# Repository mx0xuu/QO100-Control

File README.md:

# QO100-Control
Transverter control for QO100

## What is it ?
PIC based controller which will generate the required frequencies for both up-converter (DX Patrol) and down-converter. This controller will also use the PTT (SEND) from the IF Transceiver, squence the keying of RX/TX and powering of power amp.

The software is developed for PIC16F18444

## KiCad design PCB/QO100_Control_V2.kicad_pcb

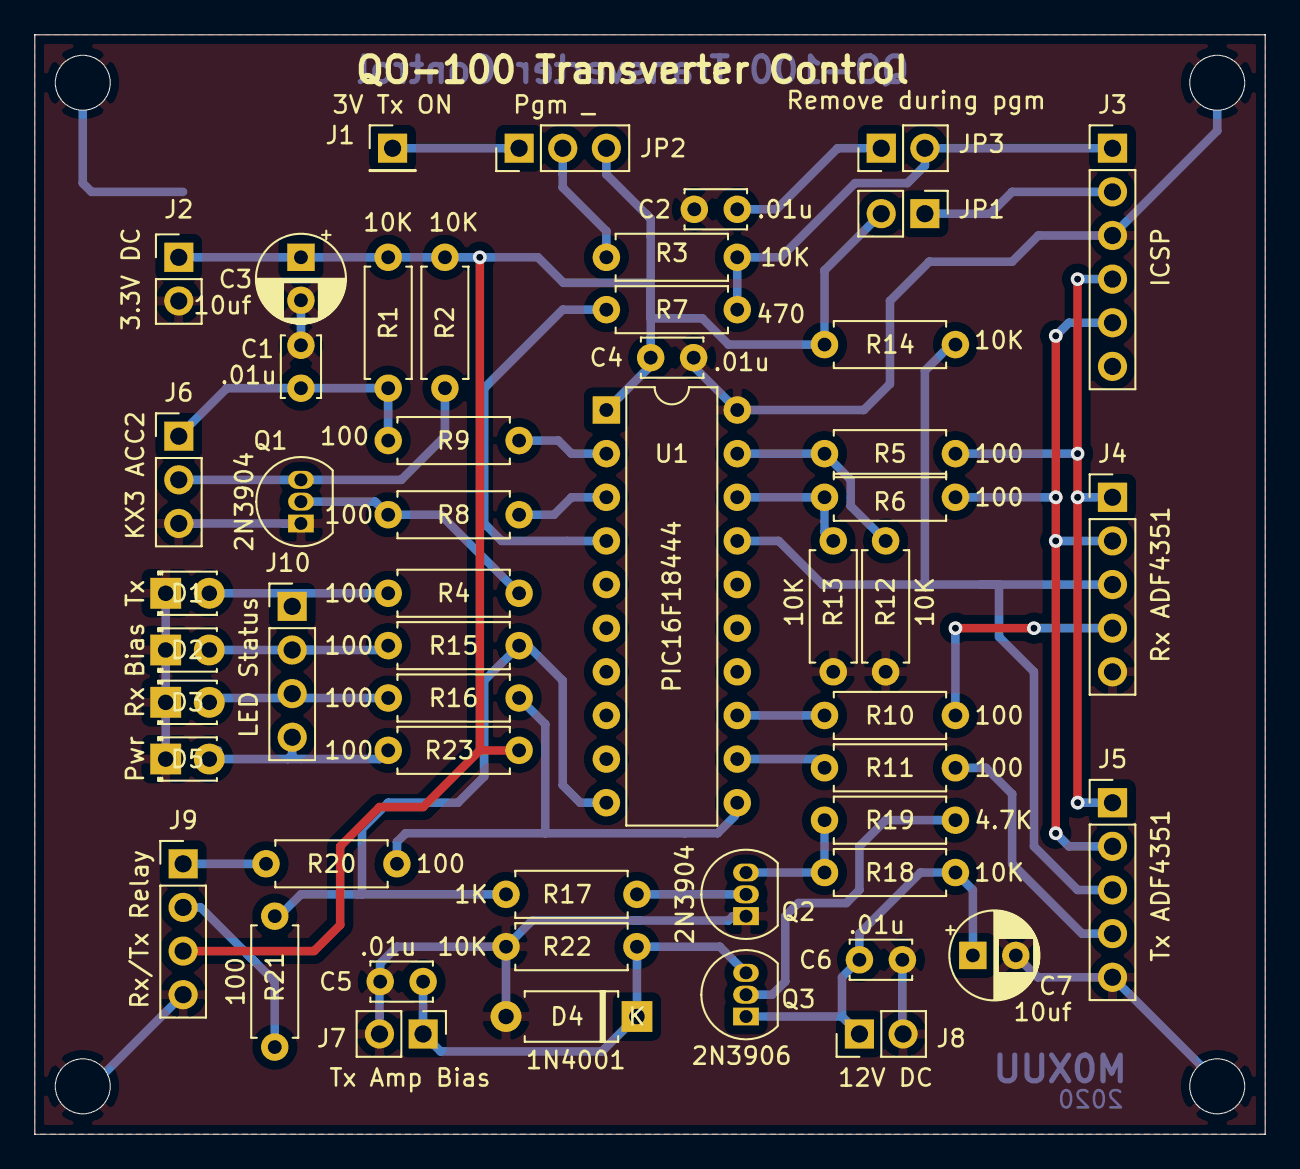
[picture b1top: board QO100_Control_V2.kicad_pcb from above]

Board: 2 copper layers, 71.6 x 64.0 mm, 56 parts (0 on the bottom side), 35 nets.

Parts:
C1, C2, C4, C5, C6: .01u; C_Disc_D3.4mm_W2.1mm_P2.50mm
C3, C7: 10uf; CP_Radial_D5.0mm_P2.50mm
D1, D2, D3, D5: LED; LED_D1.8mm_W3.3mm_H2.4mm
D4: 1N4001; D_A-405_P7.62mm_Horizontal
J1: 3V Tx ON; PinHeader_1x01_P2.54mm_Vertical
J2: 3.3V DC; PinHeader_1x02_P2.54mm_Vertical
J3: ICSP; PinHeader_1x06_P2.54mm_Vertical
J4: Rx ADF4351; PinHeader_1x05_P2.54mm_Vertical
J5: Tx ADF4351; PinHeader_1x05_P2.54mm_Vertical
J6: KX3 ACC2; PinHeader_1x03_P2.54mm_Vertical
J7: Tx Amp Bias; PinHeader_1x02_P2.54mm_Vertical
J8: 12V DC; PinHeader_1x02_P2.54mm_Vertical
J9: Rx/Tx Relay; PinHeader_1x04_P2.54mm_Vertical
J10: LED Status; PinHeader_1x04_P2.54mm_Vertical
JP1, JP3: Remove during pgm; PinHeader_1x02_P2.54mm_Vertical
JP2: Pgm _; PinHeader_1x03_P2.54mm_Vertical
Q1, Q2: 2N3904; TO-92_Inline
Q3: 2N3906; TO-92_Inline
R1, R2, R3, R12, R13, R14, R18, R22: 10K; R_Axial_DIN0207_L6.3mm_D2.5mm_P7.62mm_Horizontal
R4, R5, R6, R8, R9, R10, R11, R15, R16, R20, R21, R23: 100; R_Axial_DIN0207_L6.3mm_D2.5mm_P7.62mm_Horizontal
R7: 470; R_Axial_DIN0207_L6.3mm_D2.5mm_P7.62mm_Horizontal
R17: 1K; R_Axial_DIN0207_L6.3mm_D2.5mm_P7.62mm_Horizontal
R19: 4.7K; R_Axial_DIN0207_L6.3mm_D2.5mm_P7.62mm_Horizontal
TP1, TP2, TP3, TP4: M3; MountingHole_3.2mm_M3
U1: PIC16F18444; DIP-20_W7.62mm

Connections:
+3V3: C3.1, C4.1, J2.1, J9.3, JP1.2, JP2.3, R1.1, R2.1, R14.1, R23.1, U1.1
+12V: C6.1, C7.1, J8.1, Q3.1, R18.1
GND: C1.2, C2.2, C3.2, C4.2, C5.2, C6.2, C7.2, D1.1, D2.1, D3.1, D4.2, D5.1, J2.2, J3.3, J4.5, J5.5, J6.3, J7.2, J8.2, J9.4, Q1.1, Q2.1, R12.2, R13.2, R22.2, TP1.1, TP2.1, TP3.1, TP4.1, U1.20
unnamed: C1.1, J6.1, R1.2, R9.1
unnamed: C2.1, JP3.1
unnamed: C5.1, D4.1, J7.1, Q3.3, R22.1
unnamed: D1.2, J10.1, R4.1
unnamed: D2.2, J10.2, R15.2
unnamed: D3.2, J10.3, R16.2
unnamed: D5.2, J10.4, R23.2
unnamed: J1.1, JP2.1
unnamed: J3.1, JP3.2, R3.2, R7.1
unnamed: J3.2, JP1.1
unnamed: J3.4, J4.1, J5.1, R5.1
unnamed: J3.5, J4.2, J5.2, R6.1
unnamed: J4.3, J5.3, R14.2, U1.17
unnamed: J4.4, R10.1
unnamed: J5.4, R11.1
unnamed: J6.2, Q1.3, R2.2
unnamed: J9.1, R20.2
unnamed: J9.2, R21.2
unnamed: JP2.2, R3.1
unnamed: Q1.2, R4.2, R8.1
unnamed: Q2.2, R17.1
unnamed: Q2.3, R18.2, R19.2
unnamed: Q3.2, R19.1
unnamed: R7.2, U1.4
unnamed: R8.2, U1.3
unnamed: R9.2, U1.2
unnamed: R10.2, U1.13
unnamed: R11.2, U1.12
unnamed: R5.2, R12.1, U1.19
unnamed: R6.2, R13.1, U1.18
unnamed: R15.1, R17.2, R21.1, U1.10
unnamed: R16.1, R20.1, U1.11
